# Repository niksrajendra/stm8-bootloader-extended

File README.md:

# STM8 Extended Bootloader

A UART bootloader and firmware project for STM8S microcontrollers. The bootloader receives firmware in fixed-size blocks, writes it to flash, and checks a CRC-8 before reporting success.

## Features

- Bootloader and application are built separately with SDCC.
- Application firmware is linked at `0x8C00`.
- Firmware updates use UART at 115200 baud, 8 data bits, no parity, and 1 stop bit.
- The included Python utility sends a binary firmware image and uses CRC-8 with polynomial `0x07`.
- MCU targets in the Makefiles: `stm8s003f3`, `stm8s005k6`, and `stm8s007c8`.

## Requirements

- GNU Make and an environment with `find` and `mkdir` (Git Bash, MSYS2, or WSL on Windows).
- SDCC with the STM8 tools (`sdcc`, `sdasstm8`, and `sdobjcopy`) on `PATH`.
- `stm8flash` for programming over an ST-Link V2.
- Python 3 and PySerial for the command-line firmware updater.

Install PySerial with:

```sh
python -m pip install pyserial
```

### Windows Git Bash

Git Bash provides the Unix-style shell commands used by the Makefiles, but it does not include GNU Make by default. Install Scoop if needed, then install Make from PowerShell:

```powershell
scoop install make
```

Close and reopen Git Bash, change to the repository root, and verify Make and the SDCC tools are available:

```sh
make --version
command -v sdcc
command -v sdasstm8
command -v sdobjcopy
```

Install SDCC for Windows separately if those tools are not found, and add its `bin` directory to your Windows `PATH`. Then build from the repository root using the same targets shown below, for example `make MCU=stm8s003f3`. Git Bash paths use `/e/...` instead of Windows drive paths such as `E:\...`.

## Build

The Makefiles default to `stm8s005k6`. Select the MCU that matches your hardware:

```sh
# Build both bootloader and application
make MCU=stm8s003f3

# Build just one target
make TARGET=bootloader MCU=stm8s003f3
make TARGET=application MCU=stm8s003f3

# Debug build
make CONFIG=debug MCU=stm8s003f3

# Remove generated build files
make clean MCU=stm8s003f3
```

Release HEX files are written to `bin/bootloader/` and `bin/application/`. Debug builds use `bin/bootloader_debug/` and `bin/application_debug/`. To produce binary images for the updater, run:

```sh
make binary MCU=stm8s003f3
```

The application binary is `bin/application/application.bin`.

## CI/CD

GitHub Actions runs Cppcheck, including its MISRA C:2012 addon, for the three MCU platform configurations currently defined in `platform.h` (`stm8s003f3`, `stm8s005k6`, and `stm8s007c8`). Analyzer findings fail the corresponding analysis job. Cppcheck's `misra-config` diagnostic is suppressed because the addon cannot resolve some MCU-specific hardware symbols; MISRA rule findings remain enabled. The build matrix attempts all six MCU entries listed in the Makefiles. The HEX and BIN files are available as workflow artifacts for 14 days. Pushing a version tag such as `v1.0.0` also creates a GitHub Release with the firmware files for each MCU attached.

## Program and Update

Program the bootloader onto a blank device using an ST-Link V2:

```sh
make TARGET=bootloader MCU=stm8s003f3
make -C bootloader flash MCU=stm8s003f3
```

To update application firmware, connect a voltage-compatible UART adapter with a common ground and crossed TX/RX. Hold PD4 low while resetting the target to enter bootloader mode, then run:

```sh
python utility/boot.py --port COM3 bin/application/application.bin
```

Replace `COM3` with the serial port for your adapter. The utility toggles DTR during startup; whether that resets the target depends on the adapter and board wiring. Keep the boot-entry pin low across that reset. On Linux, a port such as `/dev/ttyUSB0` can be used instead.

## Block-Size Compatibility

The firmware uses 64-byte blocks for STM8S003F3 and 128-byte blocks for STM8S005K6/STM8S007C8. The included Python and Qt utilities currently use 64-byte blocks. Therefore, the included updater currently matches the STM8S003F3 build; do not use it with the 128-byte firmware builds without first updating the utility to use the matching block size.

## Repository Layout

- `bootloader/`: bootloader firmware, peripheral drivers, and its Makefile.
- `application/`: example application and its Makefile.
- `utility/boot.py`: Python serial firmware updater.
- `utility/QT_GUI/`: Qt-based updater project.
- `hardware/`: development-board schematic and PCB files.

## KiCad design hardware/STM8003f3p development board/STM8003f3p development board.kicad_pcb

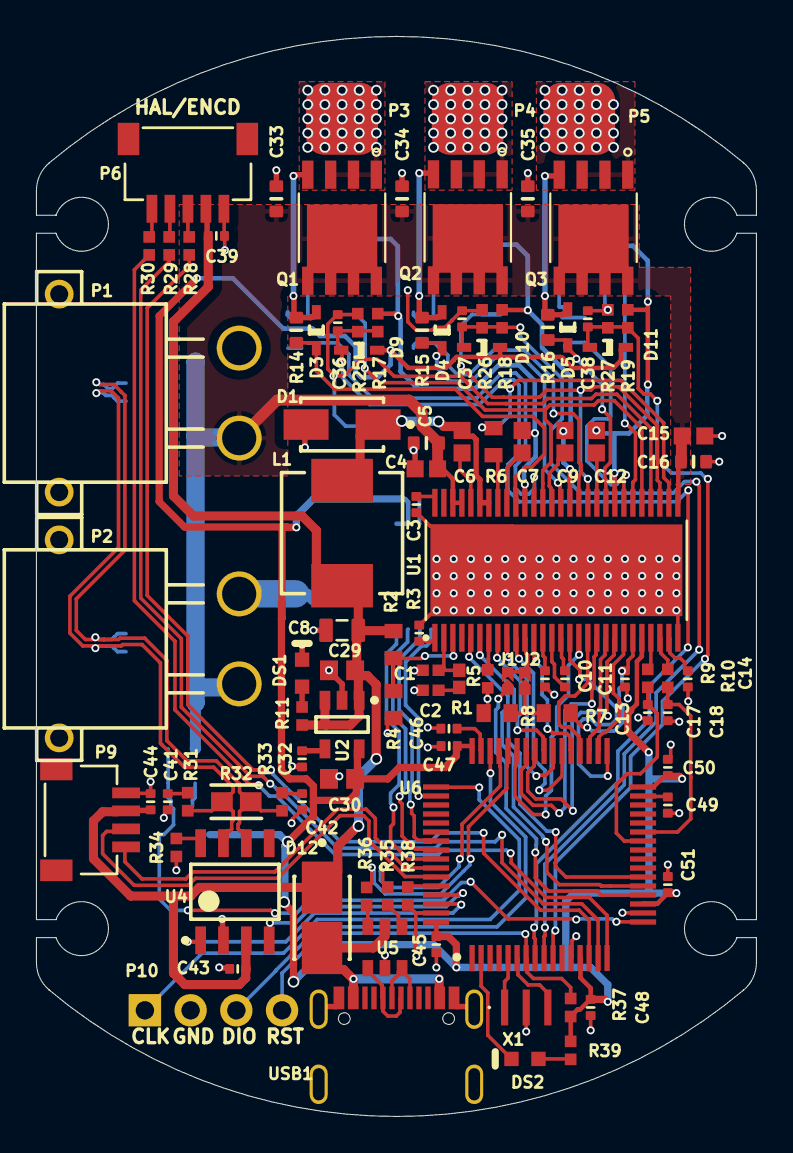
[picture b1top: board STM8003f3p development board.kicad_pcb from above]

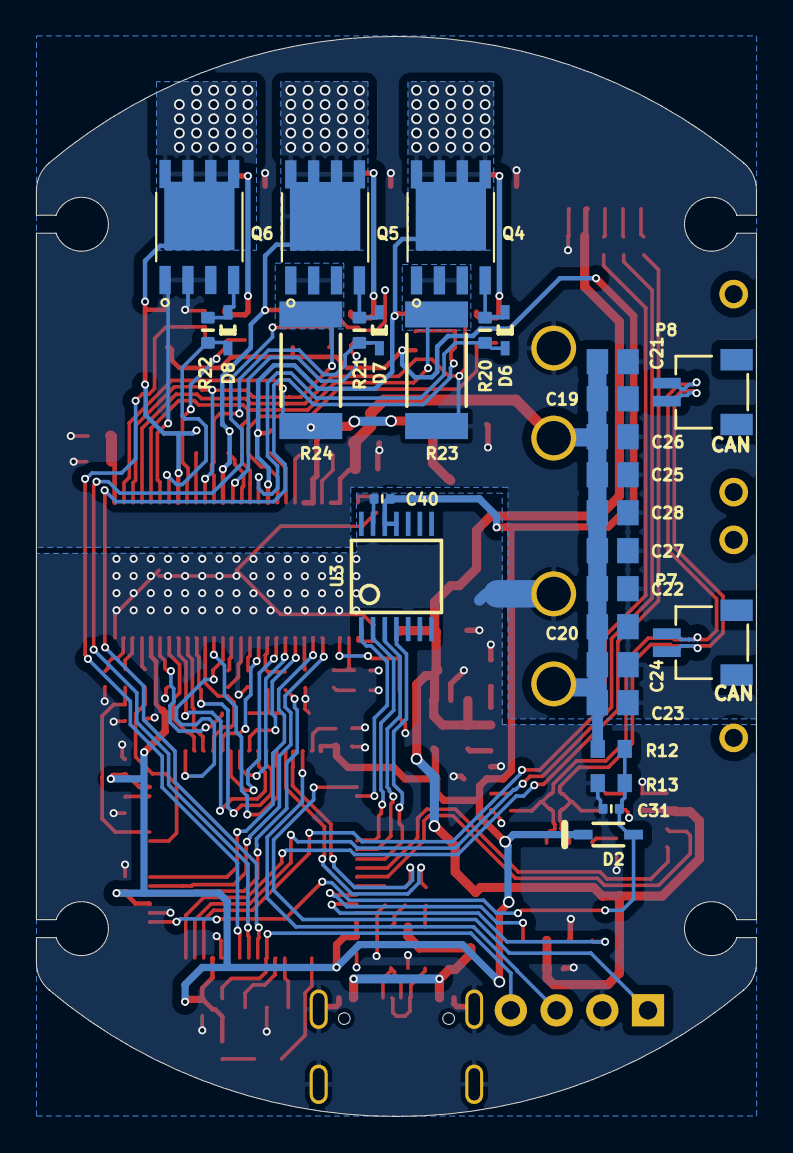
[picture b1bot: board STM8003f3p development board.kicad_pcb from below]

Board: 2 copper layers, 40.0 x 60.0 mm, 131 parts (29 on the bottom side), 100 nets.

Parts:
C1, C2: Capacitor 6.8 nF +/- 10% 16 V 0402; CAPC1005X56X25NL10T15
C3, C11, C17, C18: Capacitor 22nF +/-20% 10V 0402; CAPC0402(1005)60_L
C4, C6, C7, C9, C12, C15: Capacitor 100 nF +/-10% 50 V 0603; CAPC1608X90X40NL10T20
C5, C16, C33, C34, C35: Capacitor 4.7µF +/-20% 10V 0603; CAPC0603(1608)100_L
C8: Capacitor 47µF +/-40% 6.3V 0805; CAPC0805(2012)145_L
C10: Capacitor 2,2µF +/-20% 10V 0402; CAPC0402(1005)60_L
C13, C14: Capacitor 1µF +/-20% 10V 0402; CAPC0402(1005)60_L
C19, C20, C21, C22, C23, C24, C25, C26, C27, C28: Capacitor 10 uF +/- 10% 16 V 0805; CAPC2013X135X45NL10T25
C29, C30: Capacitor 1uF +/- 10% 16V 0603; CAPC1608X90X35ML15T15
C31, C36, C37, C38, C39, C40, C41, C42, C43, C44, C45, C46, C47, C48, C49, C50, C51: Capacitor 100nF +/-20% 50V 0402; CAPC0402(1005)60_L
C32: Capacitor 10nF +/-20% 50V 0402; CAPC0402(1005)60_L
D1: B330A-13-F; FP-SMA-MFG
D2: 1N4148WS; FAIR-SOD-323_V
D3, D4, D5, D6, D7, D8, D9, D10, D11: 1N4148WT; FAIR-SOD-523F-2_V
D12: 1N4007 SMD; FP-1N4007_SMD-IPC_A
DS1: HSMH-C190; AVAG-HSMX-C190_V
DS2: LTST-C190KSKT; LTST-C190KSKT_V
J1, J2: JUMPER
L1: 22uH; FP-IHLP-2525CZ-FP_2_413x3-MFG
P1, P2: XT30PW-M
P3, P4, P5: DP-01
P6: JST_SH-05P; SH-5P-SIDE
P7, P8: JST_SH-02P; SH-2P-SIDE
P9: JST_SH-04P; SH-04-SIDE
P10: HEADER-4P; female_header-4p
Q1, Q2, Q3, Q4, Q5, Q6: MDU1512RH; PDFN56
R1: Resistor 15k +/-1% 0402 63 mW; RESC1005X40X25ML10T10
R2, R4, R6, R7, R8, R12, R13: Resistor 10k +/-1% 0603 100 mW; RESC1608X55X25ML10T15
R3: Resistor 200K +/-1 % 0402 63 mW; RESC0402(1005)_L
R5, R9, R10: Resistor 10k +/-1% 0402 100 mW; RESC1005X40X25ML05T05
R11, R17, R18, R19, R25, R26, R27, R28, R29, R30, R31, R33, R34, R35, R36, R37, R38, R39: Resistor 0R +/- 5% 0402 100 mW; RESC1005X40X25ML05T05
R14, R15, R16, R20, R21, R22: Resistor 120R +/-5 % 0603 0.1 W; RESC0603(1608)_L
R23, R24: 0.001R-2512; FP-CRCW2512-e3-MFG
R32: 120R(0603); FP-RMCF0603-IPC_A
U1: DRV8302; HTSSOP-56
U2: LP2985-33DBVR; TI-DBV5_V
U3: AS5047P; TSSOP-14
U4: MCP2551-I/SN; MCHP-SN8_V
U5: USBLC6-2SC6Y; SOT23-6
U6: STM32F405RGT6; QFP50P1200X1200X160-64N
USB1: USB-C; USB-C-A40-00119
X1: 12MHz; MURA-CSTCE_G_V

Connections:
+3V3: C30.2, C40.2, C45.2, C47.2, C48.2, C50.2, C51.2, D2.2, D9.1, D10.1, D11.1, R37.1, R39.1, U1.24, U2.5, U3.11, U3.12, U6.13, U6.19, U6.32, U6.48, U6.64
+5V: C8.1, C29.2, C39.2, C43.2, C44.2, D12.1, L1.2, P6.2, P9.2, R2.2, R11.1, U2.1, U2.3, U4.3
A_SENSE: C36.2, D9.2, R17.1, R25.2, U6.8
BOOT0: R38.1, U6.60
B_SENSE: C37.2, D10.2, R18.1, R26.2, U6.9
CAN1_N: P7.2, P8.2, R32.1, R33.1, U4.6
CAN1_P: P7.1, P8.1, R31.1, R32.2, U4.7
CAN1_RX: U4.4, U6.61
CAN1_TX: U4.1, U6.62
C_SENSE: C38.2, D11.2, R19.1, R27.2, U6.10
DC_CAL: U1.12, U6.37
EN_GATE: U1.16, U6.33
GAIN: U1.10, U6.38
GH_A: D3.1, R14.1, U1.47
GH_B: D4.1, R15.1, U1.42
GH_C: D5.1, R16.1, U1.37
GL_A: D6.1, R20.1, U1.45
GL_B: D7.1, R21.1, U1.40
GL_C: D8.1, R22.1, U1.35
GND: C1.1, C2.1, C3.2, C4.2, C5.2, C8.2, C10.2, C13.2, C14.2, C15.2, C16.2, C17.2, C18.2, C19.1, C20.1, C21.1, C22.1, C23.1, C24.1, C25.1, C26.1, C27.1, C28.1, C29.1, C30.1, C31.1, C32.1, C33.2, C34.2, C35.2, C36.1, C37.1, C38.1, C39.1, C40.1, C41.1, C42.1, C43.1, C44.1, C45.1, C46.1, C47.1, C48.1, C49.1, C50.1, C51.1, D1.2, DS1.2, P1.2, P2.2, P6.1, P9.1, P10.2, Q6.1, Q6.2, Q6.3, R3.1, R4.1, R5.2, R6.2, R8.1, R13.2, R23.2, R24.2, R25.1, R26.1, R27.1, R34.1, R38.2, U1.28, U1.30, U1.32, U1.34, U1.EXP, U2.2, U3.5, U3.13, U4.2, U5.2, U6.12, U6.18, U6.63, USB1.1, USB1.12, USB1.A, USB1.B, USB1.C, USB1.D, X1.2
HAL_A: R28.2, U6.14
HAL_B: R29.2, U6.15
HAL_C: R30.2, U6.16
INH_A: U1.17, U6.43
INH_B: U1.19, U6.42
INH_C: U1.21, U6.41
INL_A: U1.18, U6.36
INL_B: U1.20, U6.35
INL_C: U1.22, U6.34
LED: DS2.2, U6.2
M_OC: U1.9, U6.39
M_PWM: U1.8, U6.40
NRST: P10.4, R37.2, U6.7
NetC1_2: C1.2, R1.2, U1.2
NetC2_2: C2.2, R1.1
NetC3_1: C3.1, U1.56
NetC6_1: C6.1, U1.52
NetC6_2: C6.2, D1.1, L1.1, U1.50, U1.51
NetC7_1: C7.1, U1.48
NetC9_1: C9.1, U1.43
NetC10_1: C10.1, U1.13
NetC11_1: C11.1, U1.14
NetC11_2: C11.2, U1.15
NetC12_1: C12.1, U1.38
NetC13_1: C13.1, R7.2, U1.23
NetC14_1: C14.1, U1.27
NetC32_2: C32.2, U2.4
NetC41_2: C41.2, R31.2
NetC42_2: C42.2, R33.2
NetC46_2: C46.2, U6.47
NetC49_2: C49.2, U6.31
NetD3_2: D3.2, Q1.4, R14.2
NetD4_2: D4.2, Q2.4, R15.2
NetD5_2: D5.2, Q3.4, R16.2
NetD6_2: D6.2, Q4.4, R20.2
NetD7_2: D7.2, Q5.4, R21.2
NetD8_2: D8.2, Q6.4, R22.2
NetDS1_1: DS1.1, R11.2
NetDS2_1: DS2.1, R39.2
NetJ1_2: J1.2, J2.2, U1.11
NetJ2_1: J2.1, R7.1, R8.2
NetP6_3: P6.3, R28.1
NetP6_4: P6.4, R29.1
NetP6_5: P6.5, R30.1
NetR2_1: R2.1, R4.2, U1.3
NetR3_2: R3.2, U1.1
NetR5_1: R5.1, U1.7
NetR6_1: R6.1, U1.49
NetR9_1: R9.1, U1.25
NetR10_1: R10.1, U1.26
NetR34_2: R34.2, U4.8
NetR35_2: R35.2, U5.4
NetR36_2: R36.2, U5.6
NetU5_1: U5.1, USB1.5, USB1.7
NetU5_3: U5.3, USB1.6, USB1.8
OC_ADJ: J1.1, U6.20
OSC_IN: U6.5, X1.1
OSC_OUT: U6.6, X1.3
PVDD: C4.1, C5.1, C15.1, C16.1, C19.2, C20.2, C21.2, C22.2, C23.2, C24.2, C25.2, C26.2, C27.2, C28.2, C33.1, C34.1, C35.1, P1.1, P2.1, Q1.5, Q1.6, Q1.7, Q1.8, Q1.EXT, Q2.5, Q2.6, Q2.7, Q2.8, Q2.EXT, Q3.5, Q3.6, Q3.7, Q3.8, Q3.EXT, R12.1, U1.29, U1.53, U1.54
PV_SENSE: C31.2, D2.1, R12.2, R13.1, U6.17
SH_A: C7.2, P3.X, Q1.1, Q1.2, Q1.3, Q4.5, Q4.6, Q4.7, Q4.8, Q4.EXT, R17.2, U1.46
SH_B: C9.2, P4.X, Q2.1, Q2.2, Q2.3, Q5.5, Q5.6, Q5.7, Q5.8, Q5.EXT, R18.2, U1.41
SH_C: C12.2, P5.X, Q3.1, Q3.2, Q3.3, Q6.5, Q6.6, Q6.7, Q6.8, Q6.EXT, R19.2, U1.36
SL_A: Q4.1, Q4.2, Q4.3, R23.1, U1.33, U1.44
SL_B: Q5.1, Q5.2, Q5.3, R24.1, U1.31, U1.39
SO1: C17.1, R9.2, U6.26
SO2: C18.1, R10.2, U6.27
SPI_CS: U3.1, U6.50
SPI_MISO: U3.3, U6.56
SPI_MOSI: U3.4, U6.57
SPI_SCK: U3.2, U6.55
SWCLK: P10.1, U6.49
SWDIO: P10.3, U6.46
UART1_RX: P9.3, U6.59
UART1_TX: P9.4, U6.58
USB_N: R36.1, U6.44
USB_P: R35.1, U6.45
VBUS: D12.2, U5.5, USB1.2, USB1.11
nFAULT: U1.6, U6.22
nOCTW: U1.5, U6.21

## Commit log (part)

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2026-03-26 Initial commit for STM8 extended bootloader
2026-03-29 bootloader updated for SPI and GPIO module and configuration updated for STM8S003 and STM8S005
2026-03-31 bootloader updated as per lujji algo
2026-05-13 GPIO header updated for all stm8 controller
2026-05-14 update Makefile for assembly file with .s extention and init.s for startup file
2026-05-17 flash and eeprom page and block info update and add stm8s007.h
2026-05-17 update uart includes
2026-05-22 added application files to test flashing by bootloader
2026-05-31 bootloader updated for application IVT redirect and makefile update
2026-06-14 issues for application jump resoved and fixes for other small issues
